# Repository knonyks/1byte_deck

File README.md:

# 1byte_deck

Miniaturowa konsola "offline" oparta na STM32 przeznaczona do gier napisanych w Web Assembly.

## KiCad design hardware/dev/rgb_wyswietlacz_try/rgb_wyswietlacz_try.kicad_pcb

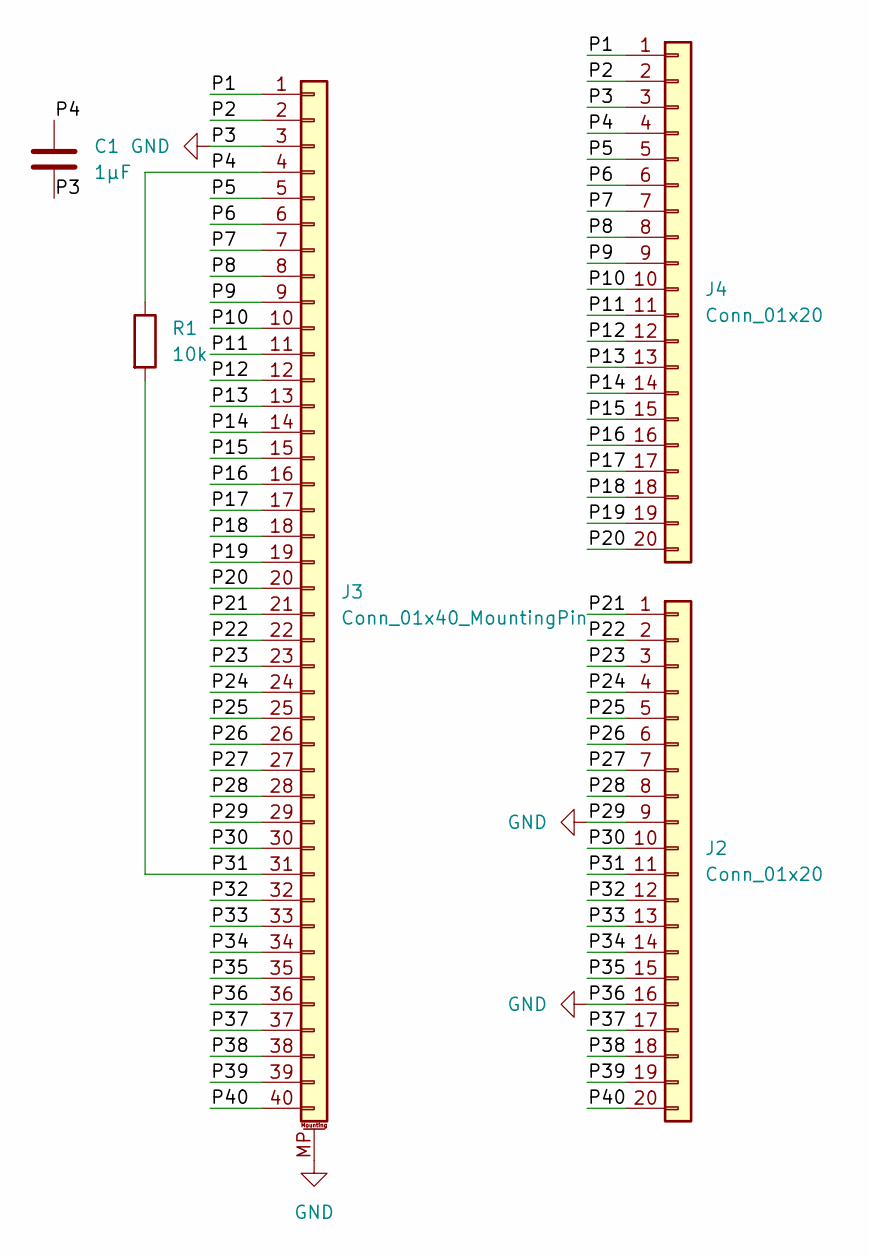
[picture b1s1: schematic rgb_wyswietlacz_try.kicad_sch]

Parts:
C1: 1µF; C_0805_2012Metric
J2, J4: Conn_01x20; PinHeader_1x20_P2.54mm_Vertical
J3: Conn_01x40_MountingPin; Hirose_FH12-40S-0.5SH_1x40-1MP_P0.50mm_Horizontal
R1: 10k; R_0805_2012Metric

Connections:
/P1: J3.1, J4.1
/P2: J3.2, J4.2
/P4: C1.1, J3.4, J4.4, R1.1
/P5: J3.5, J4.5
/P6: J3.6, J4.6
/P7: J3.7, J4.7
/P8: J3.8, J4.8
/P9: J3.9, J4.9
/P10: J3.10, J4.10
/P11: J3.11, J4.11
/P12: J3.12, J4.12
/P13: J3.13, J4.13
/P14: J3.14, J4.14
/P15: J3.15, J4.15
/P16: J3.16, J4.16
/P17: J3.17, J4.17
/P18: J3.18, J4.18
/P19: J3.19, J4.19
/P20: J3.20, J4.20
/P21: J2.1, J3.21
/P22: J2.2, J3.22
/P23: J2.3, J3.23
/P24: J2.4, J3.24
/P25: J2.5, J3.25
/P26: J2.6, J3.26
/P27: J2.7, J3.27
/P28: J2.8, J3.28
/P30: J2.10, J3.30
/P31: J2.11, J3.31, R1.2
/P32: J2.12, J3.32
/P33: J2.13, J3.33
/P34: J2.14, J3.34
/P35: J2.15, J3.35
/P37: J2.17, J3.37
/P38: J2.18, J3.38
/P39: J2.19, J3.39
/P40: J2.20, J3.40
GND: C1.2, J2.9, J2.16, J3.3, J3.29, J3.36, J3.MP (MountPin), J4.3

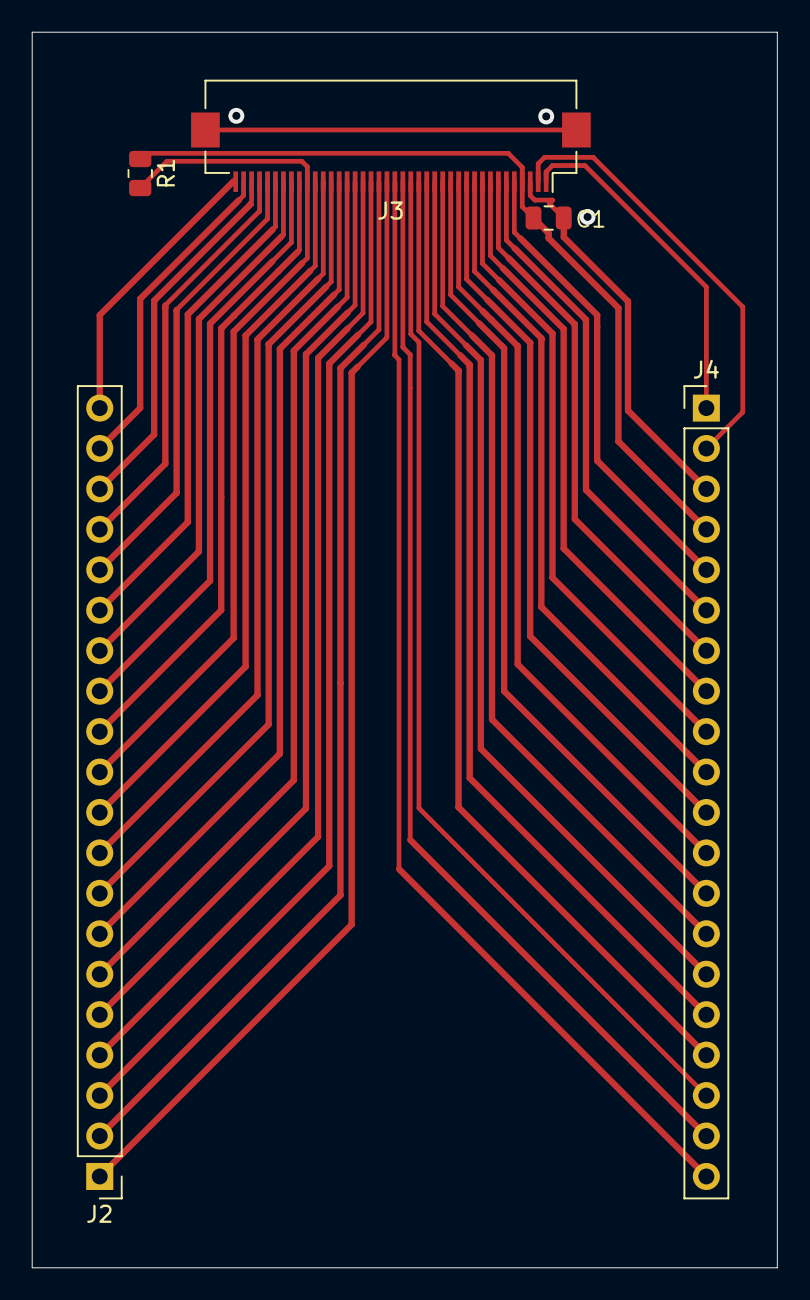
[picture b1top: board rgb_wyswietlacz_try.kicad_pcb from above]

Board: 2 copper layers, 46.8 x 77.6 mm, 5 parts (0 on the bottom side), 38 nets.

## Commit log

2026-01-12 podstawowa struktura folderów
2026-01-25 plytka rgb
